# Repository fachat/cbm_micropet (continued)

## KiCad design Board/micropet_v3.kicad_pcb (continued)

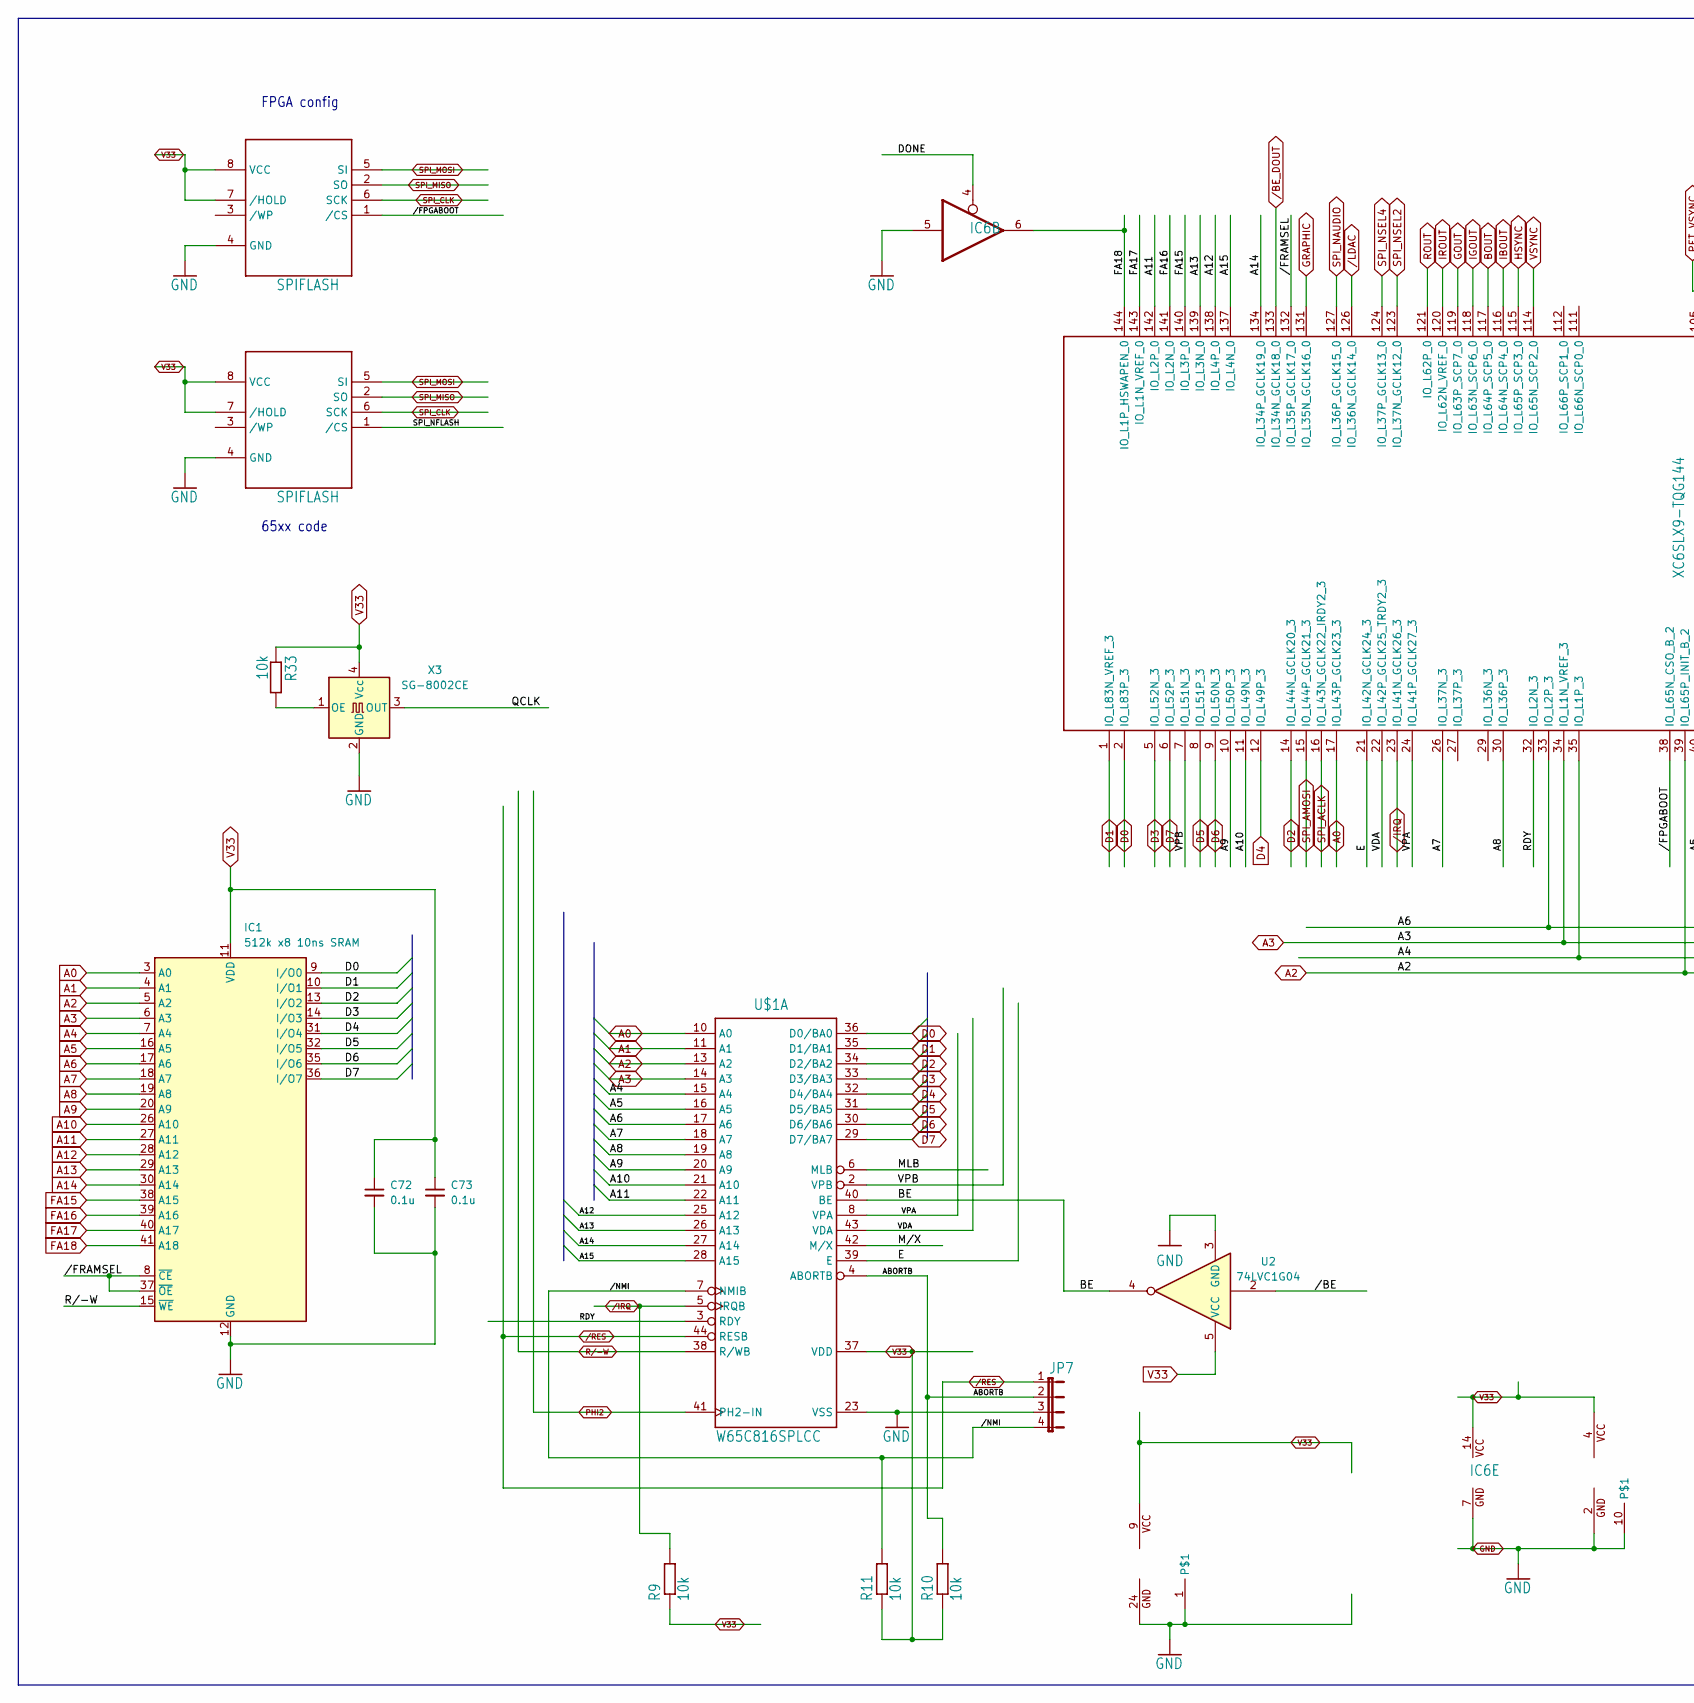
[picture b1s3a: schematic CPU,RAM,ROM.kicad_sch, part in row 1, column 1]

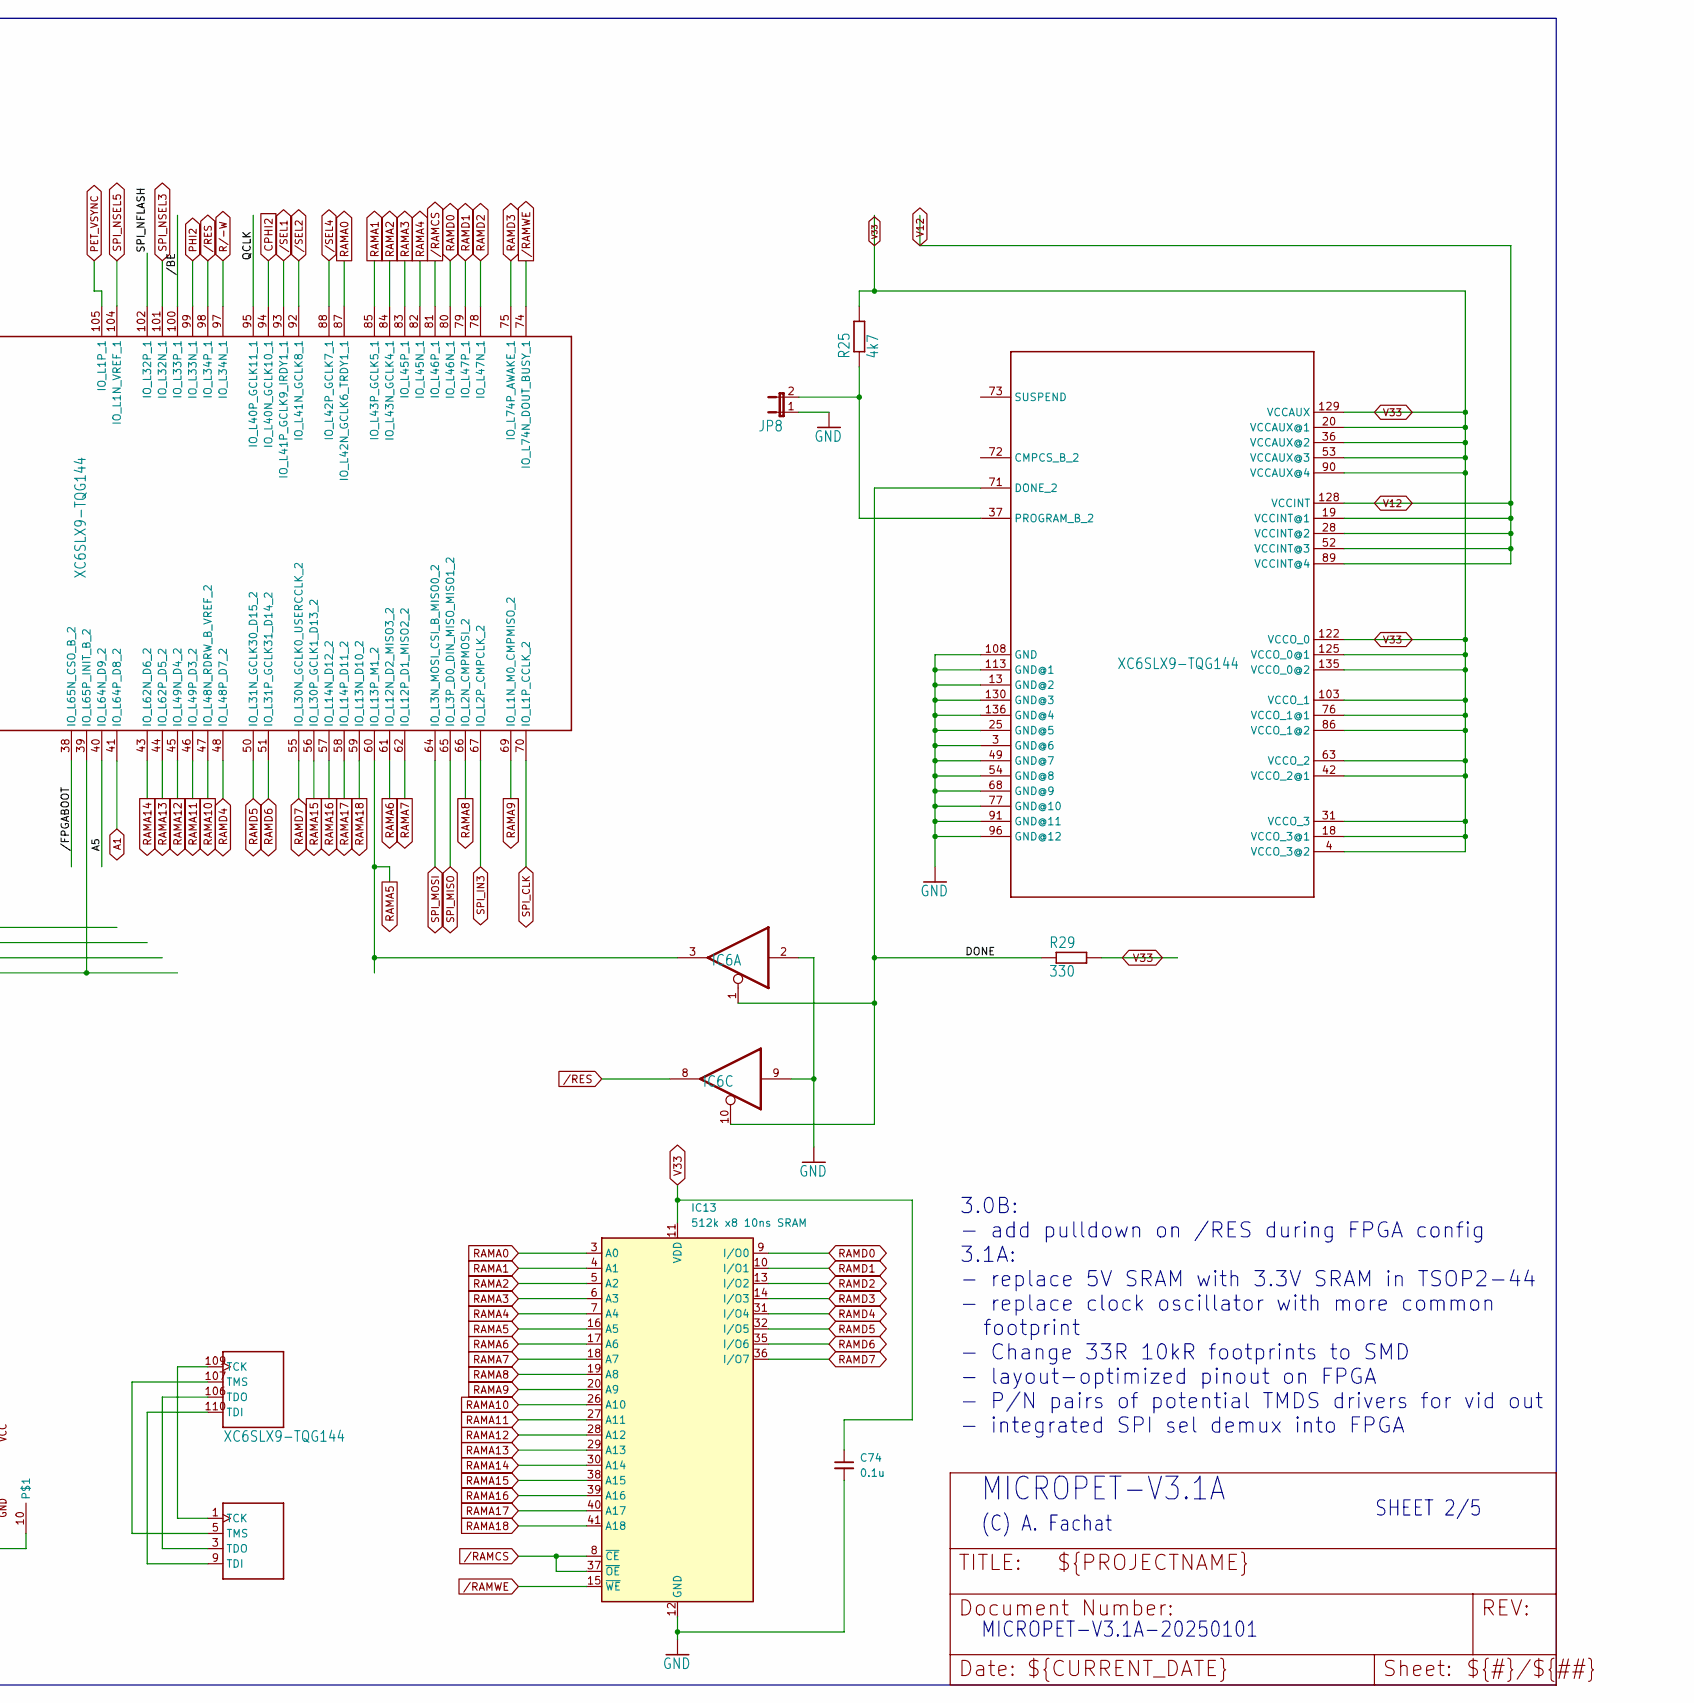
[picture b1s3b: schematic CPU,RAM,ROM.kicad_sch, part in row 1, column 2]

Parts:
C72, C73, C74: 0.1u; C_0603_1608Metric
IC1, IC13: 512k x8 10ns SRAM; TSOP-II-44_10.16x18.41mm_P0.8mm
IC6: 74125D; SO14
JP7: JP4E; JP4
JP8: JP1E; JP1
R9, R10, R11, R33: 10k; R_0805_2012Metric_Pad1.20x1.40mm_HandSolder
R25: 4k7; 0207_2V
R29: 330; 0207_2V
U2: 74LVC1G04; SOT-23-5
U$1: W65C816SPLCC; PLCC44
U$2: XC6SLX9-TQG144; TQFP144
U$4, U$14: SPIFLASH; DIL08
U$7: XILINXPROG; FLAT10BOX
X3: SG-8002CE; Oscillator_SMD_SeikoEpson_SG8002CE-4Pin_3.2x2.5mm

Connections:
/CPU,RAM,ROM/A15: U$1.28 (A15), U$2.137 (IO_L4N_0)
/CPU,RAM,ROM/ABORTB: JP7.2, R10.2, U$1.4 (ABORTB)
/CPU,RAM,ROM/BE: U2.4, U$1.40 (BE)
/CPU,RAM,ROM/DONE: IC6.1 (OE), IC6.4 (OE), IC6.10 (OE), R29.1, U$2.71 (DONE_2)
/CPU,RAM,ROM/E: U$1.39 (E), U$2.21 (IO_L42N_GCLK24_3)
/CPU,RAM,ROM/MLB: U$1.6 (MLB)
/CPU,RAM,ROM/M/X: U$1.42 (M/X)
/CPU,RAM,ROM/QCLK: U$2.95 (IO_L40P_GCLK11_1), X3.3 (OUT)
/CPU,RAM,ROM/RDY: U$1.3 (RDY), U$2.32 (IO_L2N_3)
/CPU,RAM,ROM/SPI_NFLASH: U$2.102 (IO_L32P_1), U$4.1 (/CS)
/CPU,RAM,ROM/VDA: U$1.43 (VDA), U$2.22 (IO_L42P_GCLK25_TRDY2_3)
/CPU,RAM,ROM/VPA: U$1.8 (VPA), U$2.24 (IO_L41P_GCLK27_3)
/CPU,RAM,ROM/VPB: U$1.2 (VPB), U$2.7 (IO_L51N_3)
/CPU,RAM,ROM//BE: U2.2, U$2.100 (IO_L33P_1)
/CPU,RAM,ROM//NMI: JP7.4, R11.2, U$1.7 (NMIB)
A0: IC1.3 (A0), U$1.10 (A0), U$2.17 (IO_L43P_GCLK23_3); also elsewhere on the board
A1: IC1.4 (A1), U$1.11 (A1), U$2.41 (IO_L64P_D8_2); also elsewhere on the board
A2: IC1.5 (A2), U$1.13 (A2), U$2.39 (IO_L65P_INIT_B_2); also elsewhere on the board
A3: IC1.6 (A3), U$1.14 (A3), U$2.34 (IO_L1N_VREF_3); also elsewhere on the board
A4: IC1.7 (A4), U$1.15 (A4), U$2.35 (IO_L1P_3)
A5: IC1.16 (A5), U$1.16 (A5), U$2.40 (IO_L64N_D9_2)
A6: IC1.17 (A6), U$1.17 (A6), U$2.33 (IO_L2P_3)
A7: IC1.18 (A7), U$1.18 (A7), U$2.26 (IO_L37N_3)
A8: IC1.19 (A8), U$1.19 (A8), U$2.30 (IO_L36P_3)
A9: IC1.20 (A9), U$1.20 (A9), U$2.10 (IO_L50P_3)
A10: IC1.26 (A10), U$1.21 (A10), U$2.11 (IO_L49N_3)
A11: IC1.27 (A11), U$1.22 (A11), U$2.142 (IO_L2P_0)
A12: IC1.28 (A12), U$1.25 (A12), U$2.138 (IO_L4P_0)
A13: IC1.29 (A13), U$1.26 (A13), U$2.139 (IO_L3N_0)
A14: IC1.30 (A14), U$1.27 (A14), U$2.134 (IO_L34P_GCLK19_0)
BOUT: U$2.117 (IO_L64P_SCP5_0); also elsewhere on the board
CPHI2: U$2.94 (IO_L40N_GCLK10_1); also elsewhere on the board
D0: IC1.9 (I/O0), U$1.36 (D0/BA0), U$2.2 (IO_L83P_3); also elsewhere on the board
D1: IC1.10 (I/O1), U$1.35 (D1/BA1), U$2.1 (IO_L83N_VREF_3); also elsewhere on the board
D2: IC1.13 (I/O2), U$1.34 (D2/BA2), U$2.14 (IO_L44N_GCLK20_3); also elsewhere on the board
D3: IC1.14 (I/O3), U$1.33 (D3/BA3), U$2.5 (IO_L52N_3); also elsewhere on the board
D4: IC1.31 (I/O4), U$1.32 (D4/BA4), U$2.12 (IO_L49P_3); also elsewhere on the board
D5: IC1.32 (I/O5), U$1.31 (D5/BA5), U$2.8 (IO_L51P_3); also elsewhere on the board
D6: IC1.35 (I/O6), U$1.30 (D6/BA6), U$2.9 (IO_L50N_3); also elsewhere on the board
D7: IC1.36 (I/O7), U$1.29 (D7/BA7), U$2.6 (IO_L52P_3); also elsewhere on the board
FA15: IC1.38 (A15), U$2.140 (IO_L3P_0)
FA16: IC1.39 (A16), U$2.141 (IO_L2N_0)
FA17: IC1.40 (A17), U$2.143 (IO_L1N_VREF_0)
FA18: IC1.41 (A18), IC6.6 (O), U$2.144 (IO_L1P_HSWAPEN_0)
GND: C72.2, C73.2, C74.2, IC1.12 (GND), IC1.34 (GND), IC6.2 (I), IC6.5 (I), IC6.7 (GND), IC6.9 (I), IC13.12 (GND), IC13.34 (GND), JP7.3, JP8.1, U2.3 (GND), U$1.1, U$1.23 (VSS), U$1.24 (GND), U$2.3 (GND@6), U$2.13 (GND@2), U$2.25 (GND@5), U$2.49 (GND@7), U$2.54 (GND@8), U$2.68 (GND@9), U$2.77 (GND@10), U$2.91 (GND@11), U$2.96 (GND@12), U$2.108 (GND), U$2.113 (GND@1), U$2.130 (GND@3), U$2.136 (GND@4), U$4.4 (GND), U$7.2 (GND), U$7.10, U$14.4 (GND), X3.2 (GND); also elsewhere on the board
GOUT: U$2.119 (IO_L63P_SCP7_0); also elsewhere on the board
GRAPHIC: U$2.131 (IO_L35N_GCLK16_0); also elsewhere on the board
HSYNC: U$2.115 (IO_L65P_SCP3_0); also elsewhere on the board
IBOUT: U$2.116 (IO_L64N_SCP4_0); also elsewhere on the board
IGOUT: U$2.118 (IO_L63N_SCP6_0); also elsewhere on the board
IROUT: U$2.120 (IO_L62N_VREF_0); also elsewhere on the board
unnamed: JP8.2, R25.1, U$2.37 (PROGRAM_B_2)
unnamed: U$2.109 (TCK), U$7.1 (TCK)
unnamed: U$2.110 (TDI), U$7.9 (TDI)
unnamed: U$2.106 (TDO), U$7.3 (TDO)
unnamed: U$2.107 (TMS), U$7.5 (TMS)
unnamed: R33.2, X3.1 (OE)
PET_VSYNC: U$2.105 (IO_L1P_1); also elsewhere on the board
PHI2: U$1.41 (PH2-IN), U$2.99 (IO_L33N_1)
RAMA0: IC13.3 (A0), U$2.87 (IO_L42N_GCLK6_TRDY1_1)
RAMA1: IC13.4 (A1), U$2.85 (IO_L43P_GCLK5_1)
RAMA2: IC13.5 (A2), U$2.84 (IO_L43N_GCLK4_1)
RAMA3: IC13.6 (A3), U$2.83 (IO_L45P_1)
RAMA4: IC13.7 (A4), U$2.82 (IO_L45N_1)
RAMA5: IC6.3 (O), IC13.16 (A5), U$2.60 (IO_L13P_M1_2)
RAMA6: IC13.17 (A6), U$2.61 (IO_L12N_D2_MISO3_2)
RAMA7: IC13.18 (A7), U$2.62 (IO_L12P_D1_MISO2_2)
RAMA8: IC13.19 (A8), U$2.66 (IO_L2N_CMPMOSI_2)
RAMA9: IC13.20 (A9), U$2.69 (IO_L1N_M0_CMPMISO_2)
RAMA10: IC13.26 (A10), U$2.47 (IO_L48N_RDRW_B_VREF_2)
RAMA11: IC13.27 (A11), U$2.46 (IO_L49P_D3_2)
RAMA12: IC13.28 (A12), U$2.45 (IO_L49N_D4_2)
RAMA13: IC13.29 (A13), U$2.44 (IO_L62P_D5_2)
RAMA14: IC13.30 (A14), U$2.43 (IO_L62N_D6_2)
RAMA15: IC13.38 (A15), U$2.56 (IO_L30P_GCLK1_D13_2)
RAMA16: IC13.39 (A16), U$2.57 (IO_L14N_D12_2)
RAMA17: IC13.40 (A17), U$2.58 (IO_L14P_D11_2)
RAMA18: IC13.41 (A18), U$2.59 (IO_L13N_D10_2)
RAMD0: IC13.9 (I/O0), U$2.80 (IO_L46N_1)
RAMD1: IC13.10 (I/O1), U$2.79 (IO_L47P_1)
RAMD2: IC13.13 (I/O2), U$2.78 (IO_L47N_1)
RAMD3: IC13.14 (I/O3), U$2.75 (IO_L74P_AWAKE_1)
RAMD4: IC13.31 (I/O4), U$2.48 (IO_L48P_D7_2)
RAMD5: IC13.32 (I/O5), U$2.50 (IO_L31N_GCLK30_D15_2)
RAMD6: IC13.35 (I/O6), U$2.51 (IO_L31P_GCLK31_D14_2)
RAMD7: IC13.36 (I/O7), U$2.55 (IO_L30N_GCLK0_USERCCLK_2)
ROUT: U$2.121 (IO_L62P_0); also elsewhere on the board
SPI_ACLK: U$2.16 (IO_L43N_GCLK22_IRDY2_3); also elsewhere on the board
SPI_AMOSI: U$2.15 (IO_L44P_GCLK21_3); also elsewhere on the board
SPI_CLK: U$2.70 (IO_L1P_CCLK_2), U$4.6 (SCK), U$14.6 (SCK); also elsewhere on the board
SPI_IN3: U$2.67 (IO_L2P_CMPCLK_2); also elsewhere on the board
SPI_MISO: U$2.65 (IO_L3P_D0_DIN_MISO_MISO1_2), U$4.2 (SO), U$14.2 (SO); also elsewhere on the board
SPI_MOSI: U$2.64 (IO_L3N_MOSI_CSI_B_MISO0_2), U$4.5 (SI), U$14.5 (SI); also elsewhere on the board
SPI_NAUDIO: U$2.127 (IO_L36P_GCLK15_0); also elsewhere on the board
SPI_NSEL2: U$2.123 (IO_L37N_GCLK12_0); also elsewhere on the board
SPI_NSEL3: U$2.101 (IO_L32N_1); also elsewhere on the board
SPI_NSEL4: U$2.124 (IO_L37P_GCLK13_0); also elsewhere on the board
SPI_NSEL5: U$2.104 (IO_L1N_VREF_1); also elsewhere on the board
V12: U$2.19 (VCCINT@1), U$2.28 (VCCINT@2), U$2.52 (VCCINT@3), U$2.89 (VCCINT@4), U$2.128 (VCCINT); also elsewhere on the board
V33: C72.1, C73.1, C74.1, IC1.11 (VDD), IC1.33 (VDD), IC6.14 (VCC), IC13.11 (VDD), IC13.33 (VDD), R9.1, R10.1, R11.1, R25.2, R29.2, R33.1, U2.5 (VCC), U$1.9 (VCC), U$1.37 (VDD), U$2.4 (VCCO_3@2), U$2.18 (VCCO_3@1), U$2.20 (VCCAUX@1), U$2.31 (VCCO_3), U$2.36 (VCCAUX@2), U$2.42 (VCCO_2@1), U$2.53 (VCCAUX@3), U$2.63 (VCCO_2), U$2.76 (VCCO_1@1), U$2.86 (VCCO_1@2), U$2.90 (VCCAUX@4), U$2.103 (VCCO_1), U$2.122 (VCCO_0), U$2.125 (VCCO_0@1), U$2.129 (VCCAUX), U$2.135 (VCCO_0@2), U$4.7 (/HOLD), U$4.8 (VCC), U$7.4 (VCC), U$14.7 (/HOLD), U$14.8 (VCC), X3.4 (Vcc); also elsewhere on the board
VSYNC: U$2.114 (IO_L65N_SCP2_0); also elsewhere on the board
/BE_DOUT: U$2.133 (IO_L34N_GCLK18_0); also elsewhere on the board
/IRQ: R9.2, U$1.5 (IRQB), U$2.23 (IO_L41N_GCLK26_3); also elsewhere on the board
/LDAC: U$2.126 (IO_L36N_GCLK14_0); also elsewhere on the board
/RAMCS: IC13.8 (~CE), IC13.37 (~OE), U$2.81 (IO_L46P_1)
/RAMWE: IC13.15 (~WE), U$2.74 (IO_L74N_DOUT_BUSY_1)
/SEL1: U$2.93 (IO_L41P_GCLK9_IRDY1_1); also elsewhere on the board
/SEL2: U$2.92 (IO_L41N_GCLK8_1); also elsewhere on the board
/SEL4: U$2.88 (IO_L42P_GCLK7_1); also elsewhere on the board

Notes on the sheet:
(C) A. Fachat
SHEET 2/5
MICROPET-V3.1A
MICROPET-V3.1A-20250101
FPGA config
3.0B: - add pulldown on /RES during FPGA config 3.1A: - replace 5V SRAM with 3.3V SRAM in TSOP2-44 - replace clock oscillator with more common footprint - Change 33R 10kR footprints to SMD - layout-optimized pinout on FPGA - P/N pairs of potential TMDS drivers for vid out - integrated SPI sel demux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
65xx code

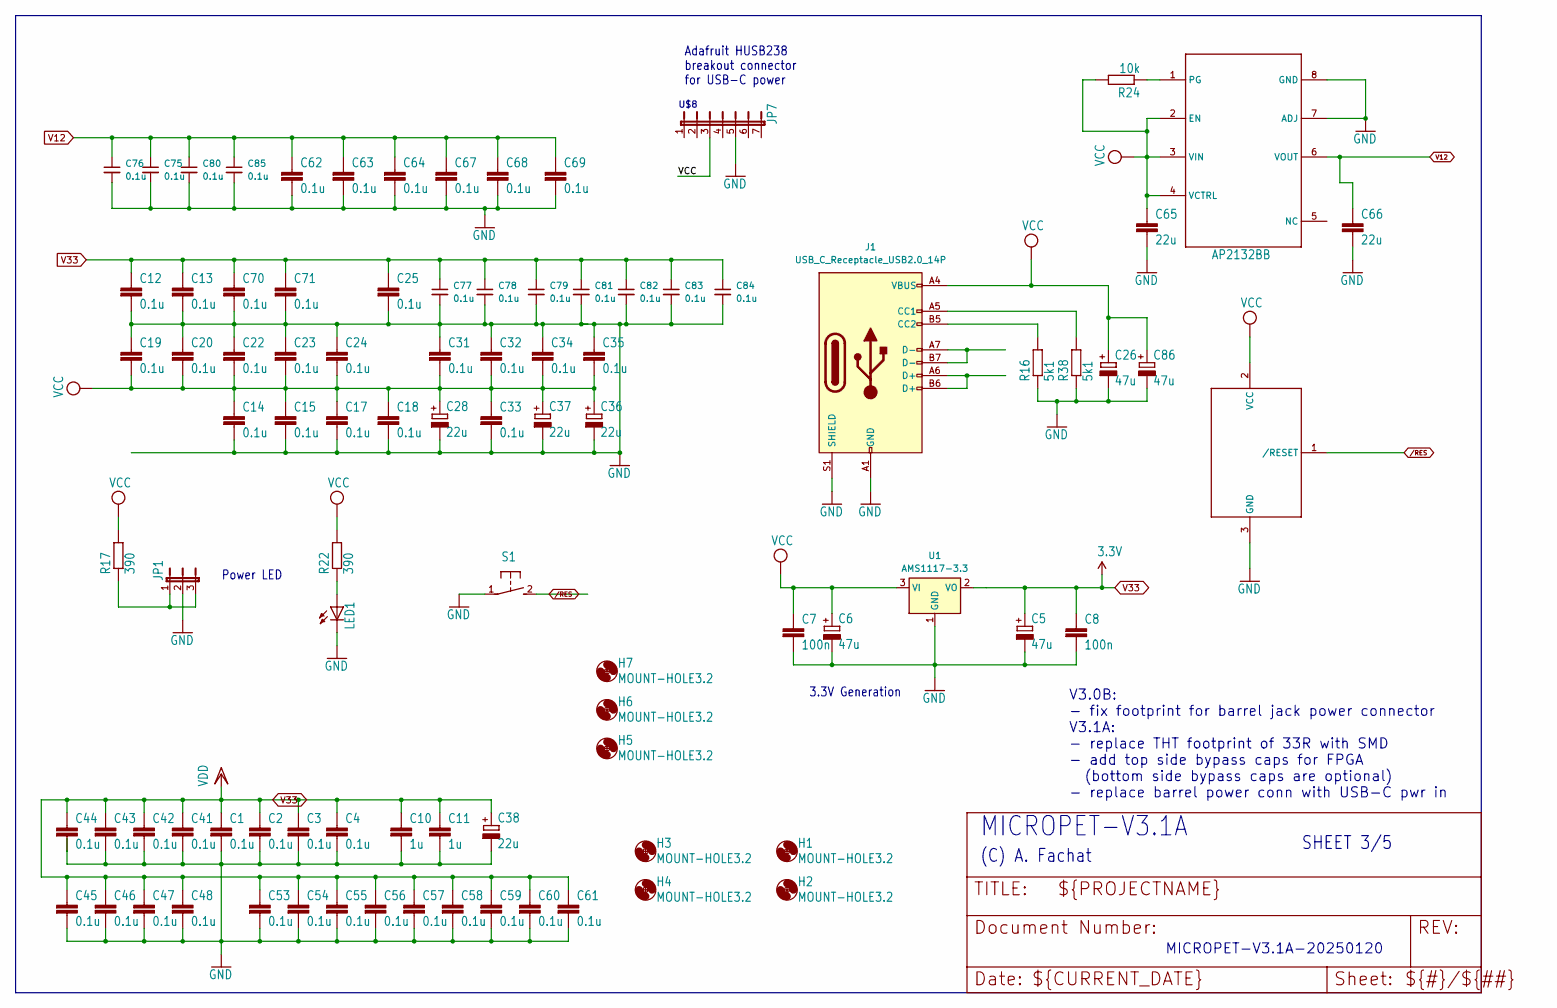
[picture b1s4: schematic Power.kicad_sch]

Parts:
C1, C2, C3, C4, C12, C13, C14, C15, C17, C18, C19, C20, C22, C23, C24, C25, C31, C32, C33, C34, C35, C41, C42, C43, C44, C45, C46, C47, C48, C53, C54, C55, C56, C57, C58, C59, C60, C61, C62, C63, C64, C67, C68, C69, C70, C71: 0.1u; C0603
C5: 47u; E5-8,5
C6, C26, C86: 47u; E5-6
C7, C8: 100n; C0603
C10, C11: 1u; C0603
C28, C36, C37, C38: 22u; E2,5-6
C65, C66: 22u; C0805
C75, C76, C77, C78, C79, C80, C81, C82, C83, C84, C85: 0.1u; C_0603_1608Metric
H1, H2, H3, H4, H5, H6, H7: MOUNT-HOLE3.2; 3,2
J1: USB_C_Receptacle_USB2.0_14P; USB_C_Receptacle_GCT_USB4085
JP1: JP2E; JP2
LED1: LED3MM
R16, R38: 5k1; 0207_2V
R17, R22: 390; 0207_2V
R24: 10k; R_0805_2012Metric_Pad1.20x1.40mm_HandSolder
S1: 31-XX; B3F-31XX
U1: AMS1117-3.3; SOT-223-3_TabPin2
U$3: DS1813; TO92
U$8: JP7; PinHeader_1x07_P2.54mm_Vertical
U$16: AP2132BB; PSOP-8-FIXED

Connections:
GND: C1.2, C2.2, C3.2, C4.2, C5.-, C6.-, C7.2, C8.2, C10.2, C11.2, C12.2, C13.2, C14.2, C15.2, C17.2, C18.2, C19.1, C20.1, C22.1, C23.1, C24.1, C25.2, C26.-, C28.-, C31.1, C32.1, C33.2, C34.1, C35.1, C36.-, C37.-, C38.-, C41.2, C42.2, C43.2, C44.2, C45.2, C46.2, C47.2, C48.2, C53.2, C54.2, C55.2, C56.2, C57.2, C58.2, C59.2, C60.2, C61.2, C62.2, C63.2, C64.2, C65.2, C66.2, C67.2, C68.2, C69.2, C70.2, C71.2, C75.2, C76.2, C77.2, C78.2, C79.2, C80.2, C81.2, C82.2, C83.2, C84.2, C85.2, C86.-, J1.A1 (GND), J1.A12 (GND), J1.B1 (GND), J1.B12 (GND), J1.S1 (SHIELD), JP1.2, LED1.K (C), R16.1, R38.1, S1.1, U1.1 (GND), U$3.3 (GND), U$8.5, U$16.7 (ADJ), U$16.8 (GND); also elsewhere on the board
unnamed: J1.A5 (CC1), R38.2
unnamed: J1.B5 (CC2), R16.2
unnamed: J1.A6 (D+), J1.B6 (D+)
unnamed: J1.A7 (D-), J1.B7 (D-)
unnamed: JP1.1, JP1.3, R17.1
unnamed: LED1.A, R22.1
unnamed: R24.1, U$16.1 (PG)
V12: C62.1, C63.1, C64.1, C66.1, C67.1, C68.1, C69.1, C75.1, C76.1, C80.1, C85.1, U$16.6 (VOUT); also elsewhere on the board
V33: C1.1, C2.1, C3.1, C4.1, C5.+, C8.1, C10.1, C11.1, C12.1, C13.1, C25.1, C38.+, C41.1, C42.1, C43.1, C44.1, C45.1, C46.1, C47.1, C48.1, C53.1, C54.1, C55.1, C56.1, C57.1, C58.1, C59.1, C60.1, C61.1, C70.1, C71.1, C77.1, C78.1, C79.1, C81.1, C82.1, C83.1, C84.1, U1.2 (VO); also elsewhere on the board
VCC: C6.+, C7.1, C14.1, C15.1, C17.1, C18.1, C19.2, C20.2, C22.2, C23.2, C24.2, C26.+, C28.+, C31.2, C32.2, C33.1, C34.2, C35.2, C36.+, C37.+, C65.1, C86.+, J1.A4 (VBUS), J1.A9 (VBUS), J1.B4 (VBUS), J1.B9 (VBUS), R17.2, R22.2, R24.2, U1.3 (VI), U$3.2 (VCC), U$8.3, U$16.2 (EN), U$16.3 (VIN), U$16.4 (VCTRL); also elsewhere on the board

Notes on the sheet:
Adafruit HUSB238 breakout connector for USB-C power
(C) A. Fachat
U$8
SHEET 3/5
V3.0B: - fix footprint for barrel jack power connector V3.1A: - replace THT footprint of 33R with SMD - add top side bypass caps for FPGA (bottom side bypass caps are optional) - replace barrel power conn with USB-C pwr in
3.3V Generation
MICROPET-V3.1A
Power LED
MICROPET-V3.1A-20250120

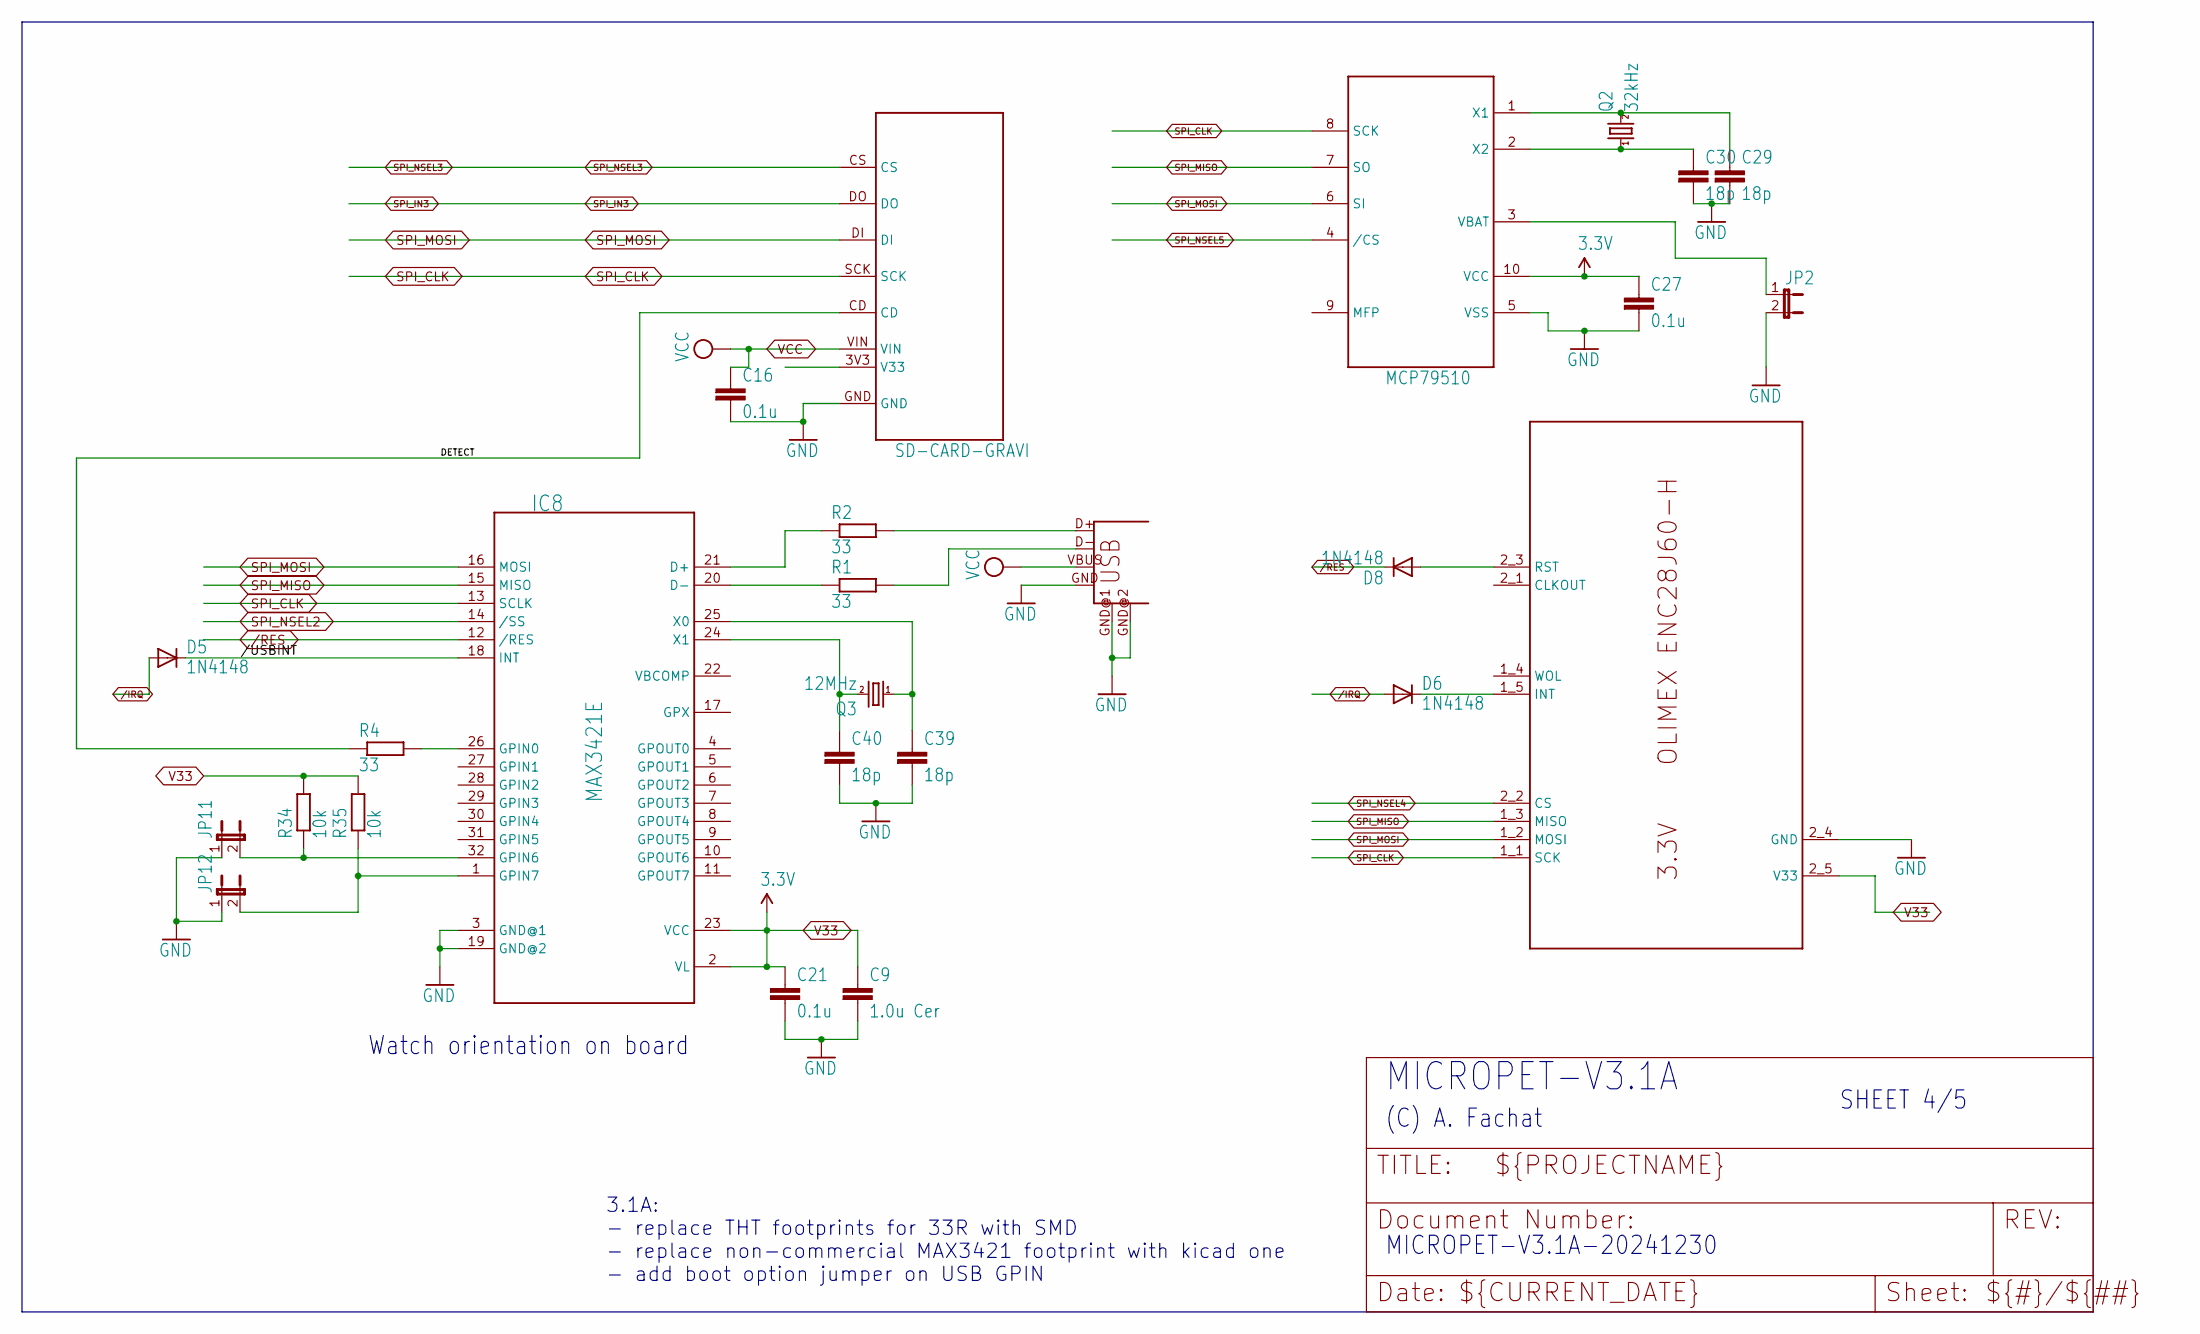
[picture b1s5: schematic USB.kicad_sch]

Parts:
C9: 1.0u Cer; C0603
C16, C21, C27: 0.1u; C0603
C29, C30, C39, C40: 18p; C0603
D5, D6, D8: 1N4148; D-5
IC8: MAX3421E; LQFP-32_5x5mm_P0.5mm
JP2, JP11, JP12: JP1E; JP1
Q2: 32kHz; TC26H
Q3: 12MHz; HC49_S
R1, R2, R4: 33; R_0805_2012Metric_Pad1.20x1.40mm_HandSolder
R34, R35: 10k; R_0805_2012Metric_Pad1.20x1.40mm_HandSolder
U$9: ETHOLIENC
U$12: SD-CARD-GRAVI; GRAVITECH-SDCARD
U$13: MCP79510; MSOP10
USB1: USB-A-H

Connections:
/USB/DETECT: R4.1, U$12.CD
/USB//USBINT: D5.C, IC8.18 (INT)
GND: C9.2, C16.2, C21.2, C27.2, C29.2, C30.2, C39.2, C40.2, IC8.3 (GND@1), IC8.19 (GND@2), JP2.2, JP11.1, JP12.1, U$9.2_4 (GND), U$12.GND, U$13.5 (VSS), USB1.GND, USB1.GND@1, USB1.GND@2; also elsewhere on the board
unnamed: IC8.21 (D+), R2.1
unnamed: IC8.20 (D-), R1.1
unnamed: IC8.26 (GPIN0), R4.2
unnamed: IC8.32 (GPIN6), JP11.2, R34.1
unnamed: IC8.1 (GPIN7), JP12.2, R35.1
unnamed: C39.1, IC8.25 (X0), Q3.1
unnamed: C40.1, IC8.24 (X1), Q3.2
unnamed: R1.2, USB1.D-
unnamed: R2.2, USB1.D+
unnamed: D6.C, U$9.1_5 (INT)
unnamed: D8.A, U$9.2_3 (RST)
unnamed: JP2.1, U$13.3 (VBAT)
unnamed: C29.1, Q2.2, U$13.1 (X1)
unnamed: C30.1, Q2.1, U$13.2 (X2)
SPI_CLK: IC8.13 (SCLK), U$9.1_1 (SCK), U$12.SCK, U$13.8 (SCK); also elsewhere on the board
SPI_IN3: U$12.DO; also elsewhere on the board
SPI_MISO: IC8.15 (MISO), U$9.1_3 (MISO), U$13.7 (SO); also elsewhere on the board
SPI_MOSI: IC8.16 (MOSI), U$9.1_2 (MOSI), U$12.DI, U$13.6 (SI); also elsewhere on the board
SPI_NSEL2: IC8.14 (/SS); also elsewhere on the board
SPI_NSEL3: U$12.CS; also elsewhere on the board
SPI_NSEL4: U$9.2_2 (CS); also elsewhere on the board
SPI_NSEL5: U$13.4 (/CS); also elsewhere on the board
V33: C9.1, C21.1, C27.1, IC8.2 (VL), IC8.23 (VCC), R34.2, R35.2, U$9.2_5 (V33), U$13.10 (VCC); also elsewhere on the board
VCC: C16.1, U$12.VIN, USB1.VBUS; also elsewhere on the board
/IRQ: D5.A, D6.A; also elsewhere on the board

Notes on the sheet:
MICROPET-V3.1A-20241230
(C) A. Fachat
Watch orientation on board~{}
MICROPET-V3.1A
3.1A: - replace THT footprints for 33R with SMD - replace non-commercial MAX3421 footprint with kicad one - add boot option jumper on USB GPIN
SHEET 4/5

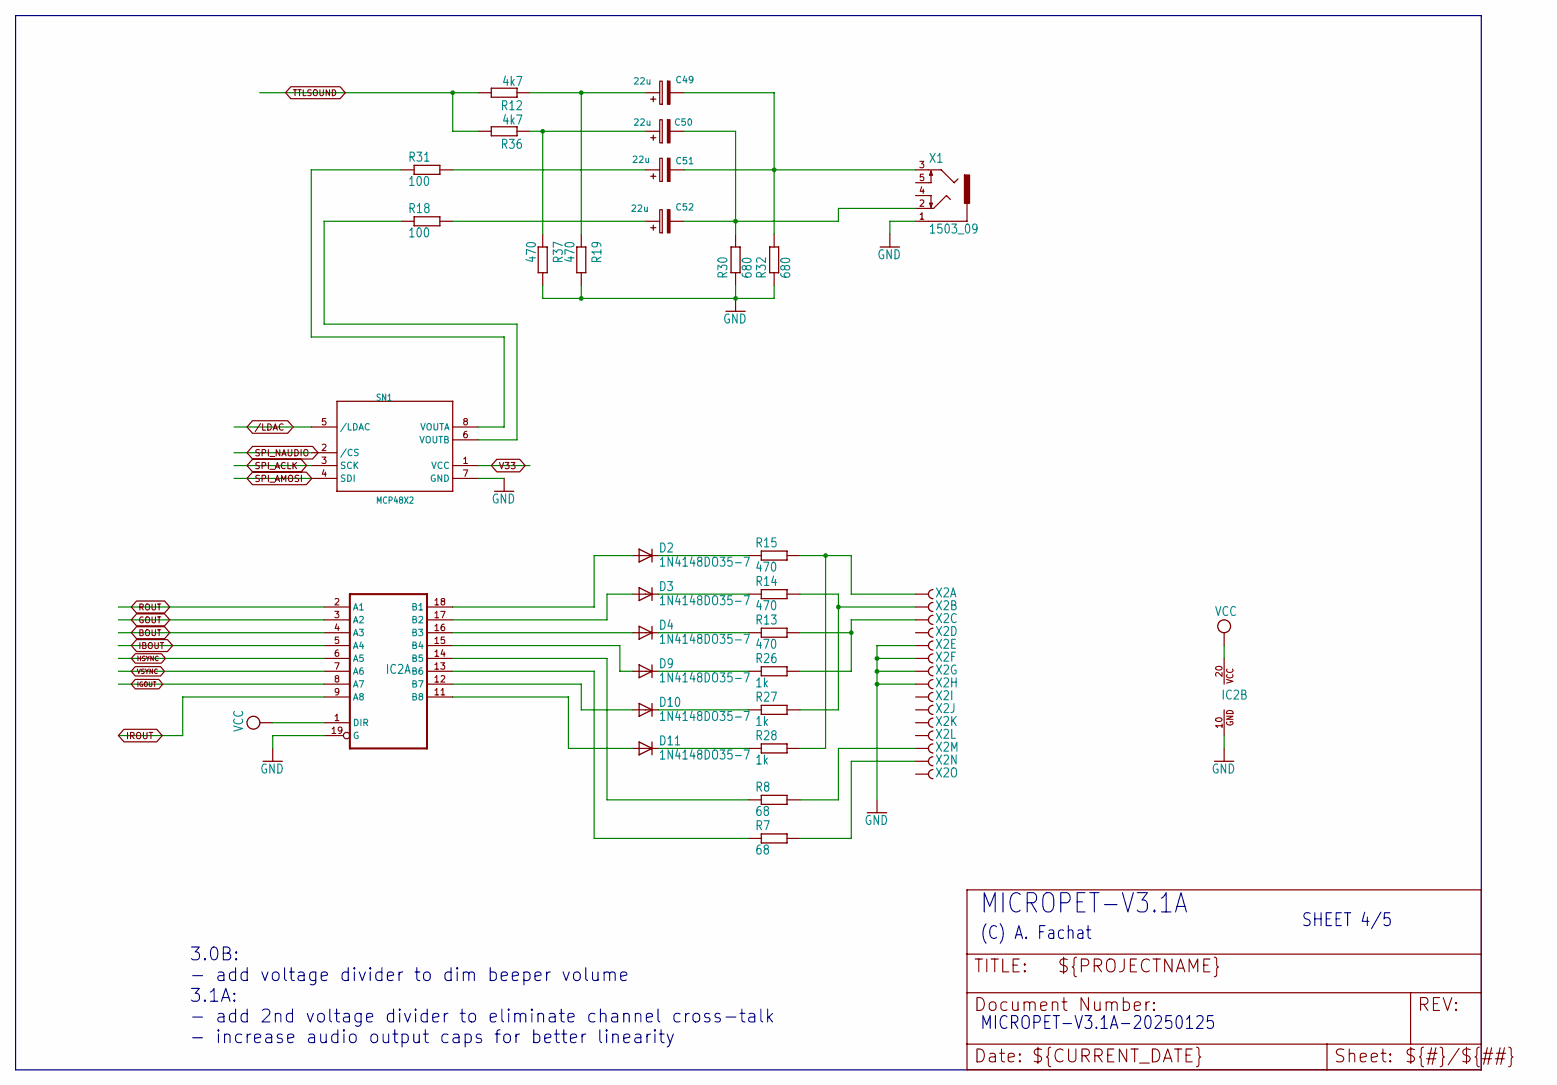
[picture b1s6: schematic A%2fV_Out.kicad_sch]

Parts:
C49, C50, C51, C52: 22u; CP_Radial_D5.0mm_P2.50mm
D2, D3, D4, D9, D10, D11: 1N4148DO35-7; DO35-7
IC2: 74245DW; SO20W
R7, R8: 68; 0204V
R12, R36: 4k7; 0204V
R13, R14, R15, R19, R37: 470; 0204V
R18, R31: 100; 0204V
R26, R27, R28: 1k; 0204V
R30, R32: 680; 0204V
SN1: MCP48X2; SOIC8
X1: 1503_09
X2: D-SUB15-HDR15RA; HDR15RA

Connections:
BOUT: IC2.4 (A3); also elsewhere on the board
GND: IC2.10 (GND), IC2.19 (G), R19.2, R30.1, R32.1, R37.2, SN1.7 (GND), X1.1, X2.5 (F), X2.6 (F), X2.7 (F), X2.8 (F); also elsewhere on the board
GOUT: IC2.3 (A2); also elsewhere on the board
HSYNC: IC2.6 (A5); also elsewhere on the board
IBOUT: IC2.5 (A4); also elsewhere on the board
IGOUT: IC2.8 (A7); also elsewhere on the board
IROUT: IC2.9 (A8); also elsewhere on the board
unnamed: C49.1, R12.1, R19.1
unnamed: C49.2, C51.2, R32.2, X1.3
unnamed: C50.1, R36.1, R37.1
unnamed: C50.2, C52.2, R30.2, X1.2
unnamed: C51.1, R31.2
unnamed: C52.1, R18.2
unnamed: D2.C, R15.1
unnamed: D3.C, R14.1
unnamed: D4.C, R13.1
unnamed: D9.C, R26.1
unnamed: D10.C, R27.1
unnamed: D11.C, R28.1
unnamed: D2.A, IC2.18 (B1)
unnamed: D3.A, IC2.17 (B2)
unnamed: D4.A, IC2.16 (B3)
unnamed: D9.A, IC2.15 (B4)
unnamed: IC2.14 (B5), R8.1
unnamed: IC2.13 (B6), R7.1
unnamed: D10.A, IC2.12 (B7)
unnamed: D11.A, IC2.11 (B8)
unnamed: R31.1, SN1.8 (VOUTA)
unnamed: R18.1, SN1.6 (VOUTB)
unnamed: R15.2, R28.2, X2.1 (F)
unnamed: R14.2, R27.2, X2.2 (F)
unnamed: R13.2, R26.2, X2.3 (F)
unnamed: R8.2, X2.13 (F)
unnamed: R7.2, X2.14 (F)
ROUT: IC2.2 (A1); also elsewhere on the board
SPI_ACLK: SN1.3 (SCK); also elsewhere on the board
SPI_AMOSI: SN1.4 (SDI); also elsewhere on the board
SPI_NAUDIO: SN1.2 (/CS); also elsewhere on the board
TTLSOUND: R12.2, R36.2; also elsewhere on the board
V33: SN1.1 (VCC); also elsewhere on the board
VCC: IC2.1 (DIR), IC2.20 (VCC); also elsewhere on the board
VSYNC: IC2.7 (A6); also elsewhere on the board
/LDAC: SN1.5 (/LDAC); also elsewhere on the board

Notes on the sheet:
3.0B: - add voltage divider to dim beeper volume 3.1A: - add 2nd voltage divider to eliminate channel cross-talk - increase audio output caps for better linearity
MICROPET-V3.1A
MICROPET-V3.1A-20250125
SHEET 4/5
(C) A. Fachat

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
